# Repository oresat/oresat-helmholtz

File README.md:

# OreSat Helmholtz Cage

This repo contains design and operating instructions of a Helmholtz Cage, which uses the [Biot Savart Law](https://en.wikipedia.org/wiki/Biot%E2%80%93Savart_law) to get a desired magnetic field inside of an enclosed space using three pairs of perpendicular coils, one pair for each axis. Our fundamental purpose in doing this is to test cubesats' pointing and detumbling capabilities in LEO.

v2.0 is now underway, utilizing less hardware than v1.0. This is excellent news for everyone involved, as less parts means less things that can and will break. We are using a Raspberry Pi Pico to run it, with each set of coils getting their own motor driver, to drive the current, and a INA226 to monitor the current. A full schematic can be found [here](./controller-v2/helmholtz-controller-v2.kicad_sch). A PCB layout is in the works.

# Design Notes

**Status, design, and testing information can be found in the [OreSat Helmholtz Cage Design Notes](https://docs.google.com/document/d/1s9UlxD-V_3-_QfmXqKaY5oYsfC2GDHxeAkWD0VgjS5g/edit?tab=t.0).**

A seperate doc on the structure and design of the cage itself can be found [here](./docs/Open%20Source%20Document.docx). This doc is a bit out of date in some aspects, mainly the technical hardware, but serves as a good resource for cage construction and theory.

## Pictures
MCECS BETA Project 2018:

Current Build:

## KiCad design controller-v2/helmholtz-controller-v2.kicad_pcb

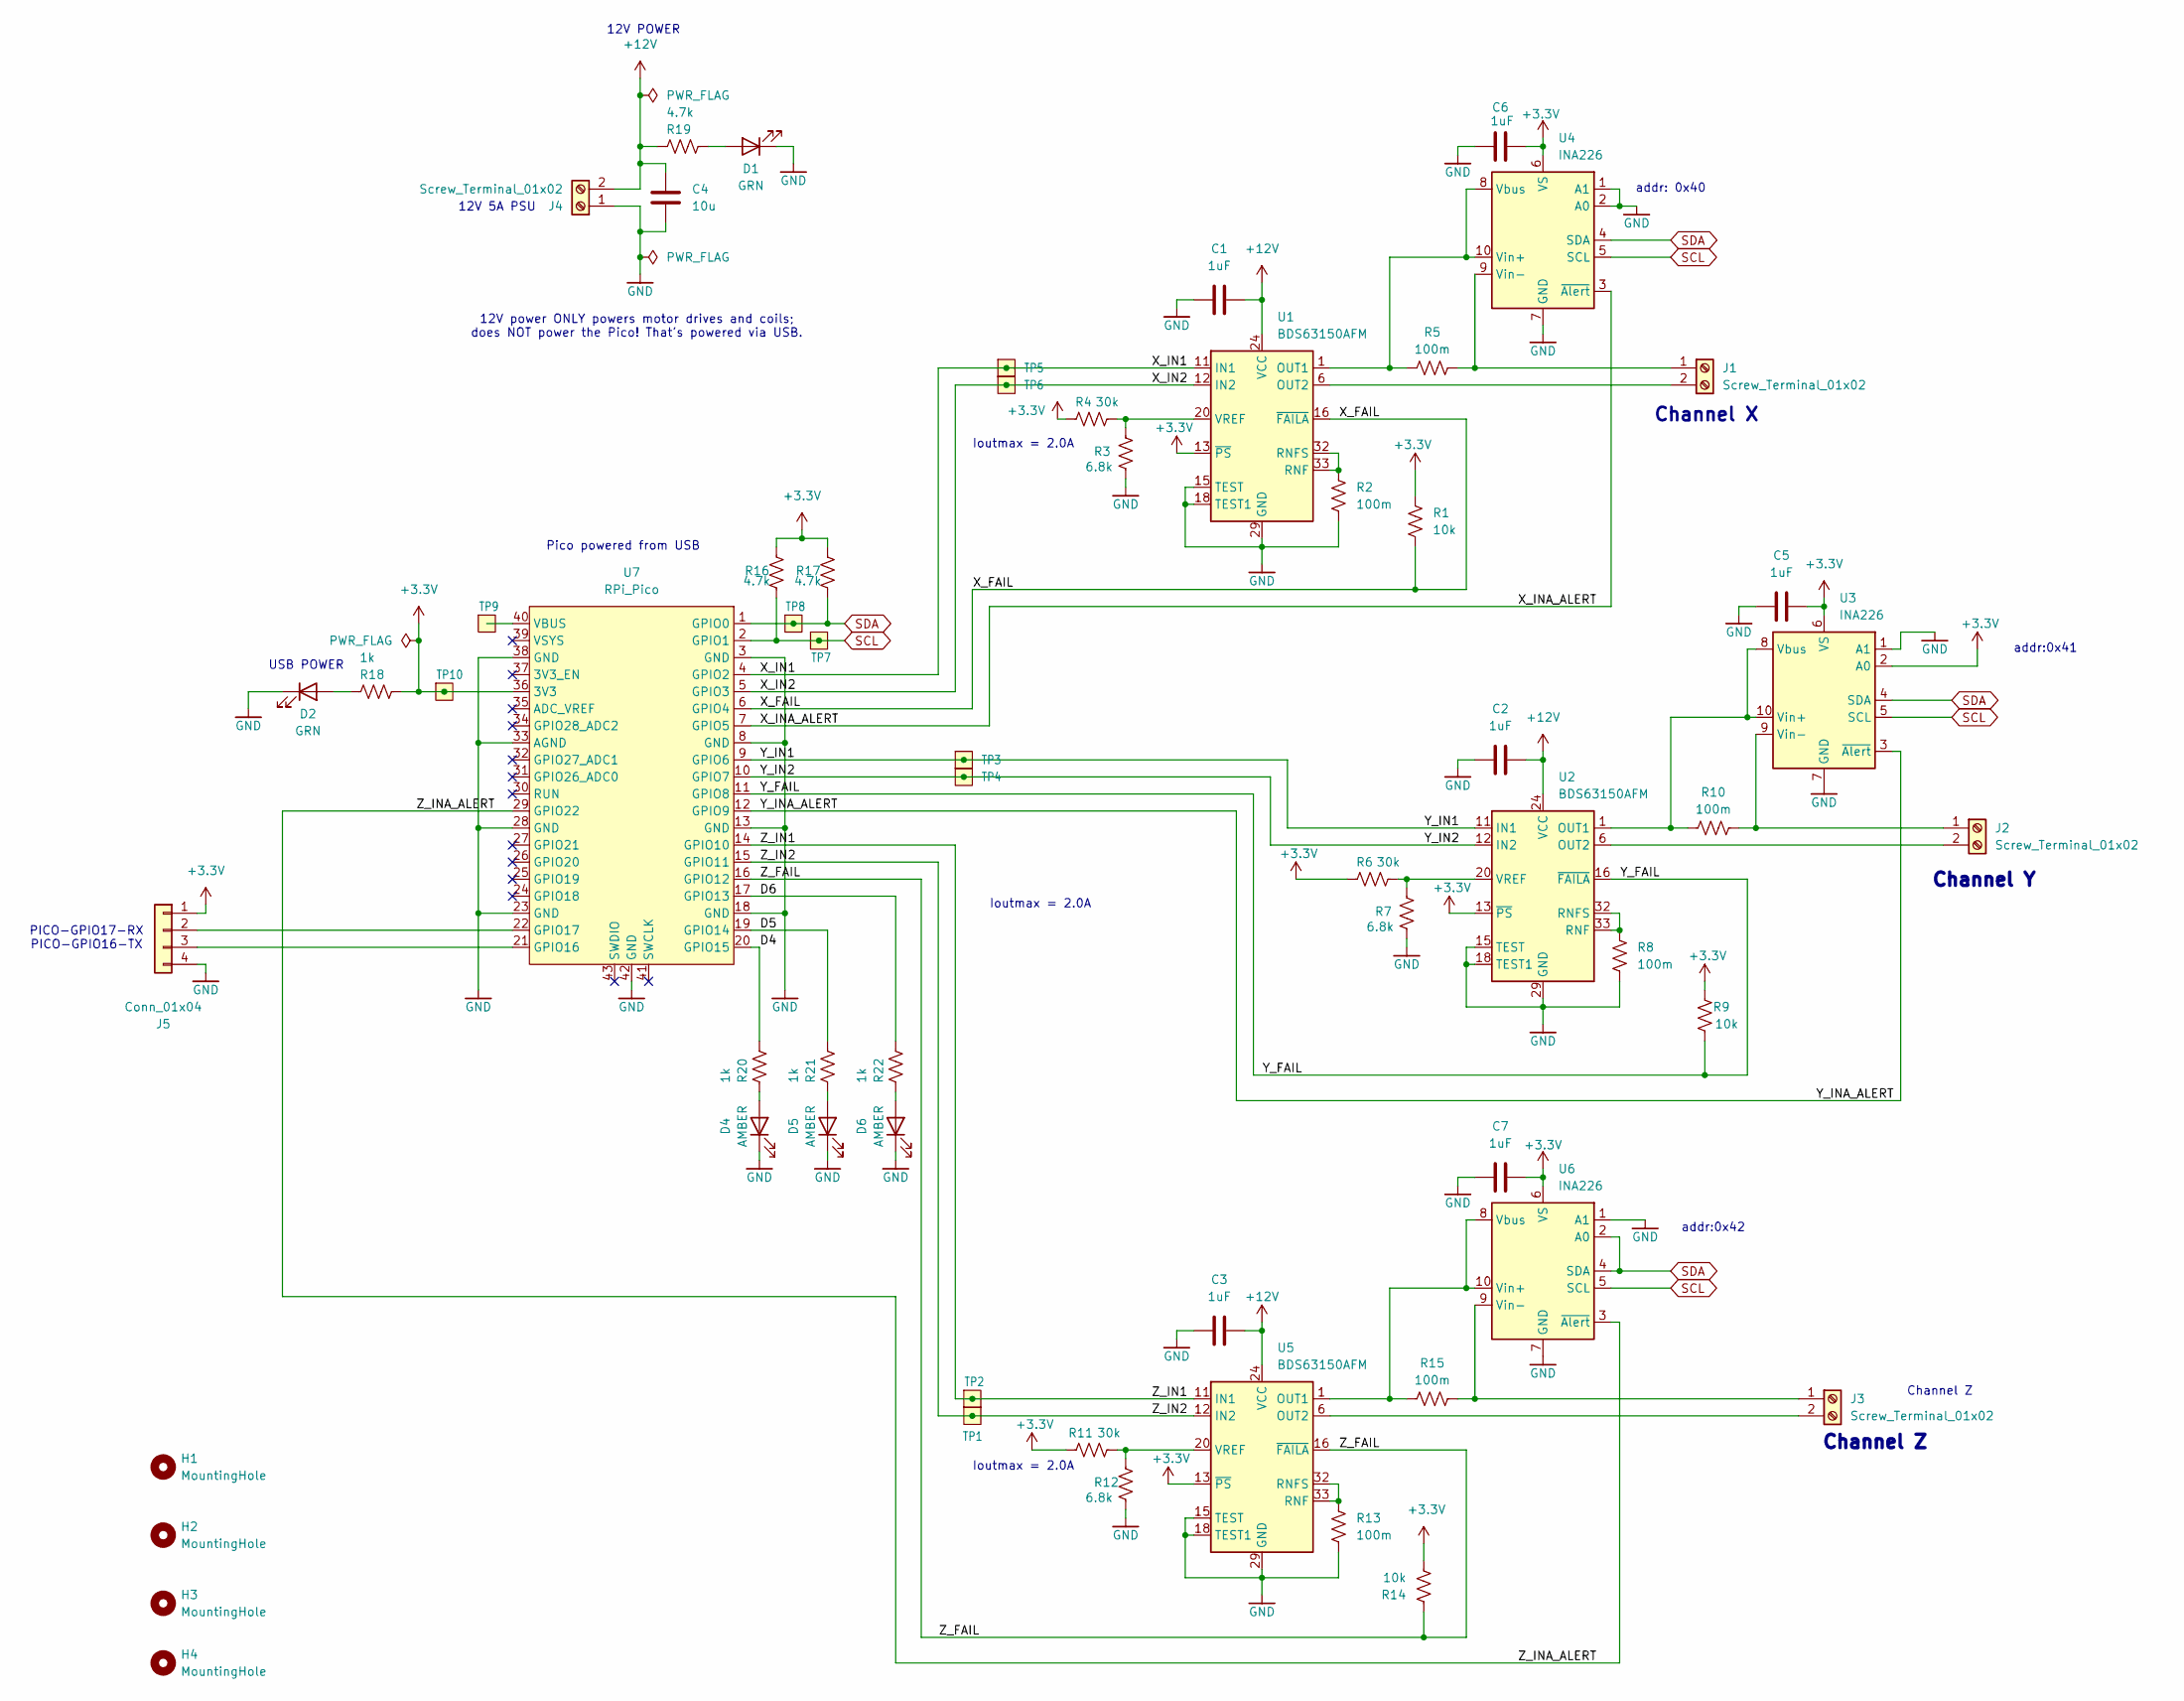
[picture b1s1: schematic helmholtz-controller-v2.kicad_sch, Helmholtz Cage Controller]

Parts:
C1, C2, C3, C5, C6, C7: 1uF; C_0805_2012Metric; MPN CL21B105KAFNNNE
C4: 10u; C_0805_2012Metric; MPN CL21A106KAYNNNE
D1, D2: GRN; LED_0603_1608Metric; MPN IN-S63AT5G
D4, D5, D6: AMBER; LED_0603_1608Metric; MPN IN-S63AT5A
H1, H2, H3, H4: MountingHole; MountingHole_3.2mm_M3
J1, J2, J3, J4: Screw_Terminal_01x02; TerminalBlock_Phoenix_PT-1,5-2-3.5-H_1x02_P3.50mm_Horizontal; MPN 1751248
J5: Conn_01x04; PinHeader_1x04_P2.54mm_Vertical; MPN 0022112042
R1, R9, R14: 10k; R_0603_1608Metric; MPN RMCF0603FT10K0
R2, R5, R8, R10, R13, R15: 100m; R_1206_3216Metric; MPN CSR1206FTR100
R3, R7, R12: 6.8k; R_0603_1608Metric; MPN RC0603JR-076K8L
R4, R6, R11: 30k; R_0603_1608Metric; MPN CRCW060330K0FKEAC
R16, R17, R19: 4.7k; R_0603_1608Metric; MPN RC0603FR-074K7L
R18, R20, R21, R22: 1k; R_0603_1608Metric; MPN RMCF0603FT1K00
TP1, TP2, TP3, TP4, TP5, TP6, TP7, TP8, TP9, TP10: Test-Point; TestPoint-0.75mm-th
U1, U2, U5: BDS63150AFM; U-BD63150AFM; MPN BD63150AFM-E2
U3, U4, U6: INA226; VSSOP-10_3x3mm_P0.5mm; MPN INA226AIDGST
U7: RPi_Pico; RPi_Pico_Castellated; MPN SC0915

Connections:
+3.3V: C5.2, C6.2, C7.2, J5.1, R1.1, R4.1, R6.1, R9.2, R11.1, R14.2, R16.2, R17.2, R18.2, TP10.1, U1.13 (~PS), U2.13 (~PS), U3.2 (A0), U3.6 (VS), U4.6 (VS), U5.13 (~PS), U6.6 (VS), U7.36 (3V3)
+12V: C1.2, C2.2, C3.2, C4.2, J4.2, R19.1, U1.24 (VCC), U1.25 (VCC), U1.26 (VCC), U2.24 (VCC), U2.25 (VCC), U2.26 (VCC), U5.24 (VCC), U5.25 (VCC), U5.26 (VCC)
/D4: R20.2, U7.20 (GPIO15)
/D5: R21.2, U7.19 (GPIO14)
/D6: R22.2, U7.17 (GPIO13)
/X_FAIL: R1.2, U1.16 (~FAILA), U7.6 (GPIO4)
/X_IN1: TP5.1, U1.11 (IN1), U7.4 (GPIO2)
/X_IN2: TP6.1, U1.12 (IN2), U7.5 (GPIO3)
/X_INA_ALERT: U4.3 (~Alert), U7.7 (GPIO5)
/Y_FAIL: R9.1, U2.16 (~FAILA), U7.11 (GPIO8)
/Y_IN1: TP3.1, U2.11 (IN1), U7.9 (GPIO6)
/Y_IN2: TP4.1, U2.12 (IN2), U7.10 (GPIO7)
/Y_INA_ALERT: U3.3 (~Alert), U7.12 (GPIO9)
/Z_FAIL: R14.1, U5.16 (~FAILA), U7.16 (GPIO12)
/Z_IN1: TP2.1, U5.11 (IN1), U7.14 (GPIO10)
/Z_IN2: TP1.1, U5.12 (IN2), U7.15 (GPIO11)
/Z_INA_ALERT: U6.3 (~Alert), U7.29 (GPIO22)
GND: C1.1, C2.1, C3.1, C4.1, C5.1, C6.1, C7.1, D1.1 (K), D2.1 (K), D4.1 (K), D5.1 (K), D6.1 (K), J4.1, J5.4, R2.2, R3.1, R7.1, R8.2, R12.1, R13.2, U1.15 (TEST), U1.18 (TEST1), U1.22 (GND), U1.29 (GND), U1.37 (GND), U1.38 (GND), U2.15 (TEST), U2.18 (TEST1), U2.22 (GND), U2.29 (GND), U2.37 (GND), U2.38 (GND), U3.1 (A1), U3.7 (GND), U4.1 (A1), U4.2 (A0), U4.7 (GND), U5.15 (TEST), U5.18 (TEST1), U5.22 (GND), U5.29 (GND), U5.37 (GND), U5.38 (GND), U6.1 (A1), U6.7 (GND), U7.3 (GND), U7.8 (GND), U7.13 (GND), U7.18 (GND), U7.23 (GND), U7.28 (GND), U7.33 (AGND), U7.38 (GND), U7.42 (GND)
unnamed: D1.2 (A), R19.2
unnamed: D2.2 (A), R18.1
unnamed: D4.2 (A), R20.1
unnamed: D5.2 (A), R21.1
unnamed: D6.2 (A), R22.1
unnamed: J1.1, R5.2, U4.9 (Vin-)
unnamed: J1.2, U1.6 (OUT2), U1.7 (OUT2), U1.8 (OUT2)
unnamed: J2.1, R10.2, U3.9 (Vin-)
unnamed: J2.2, U2.6 (OUT2), U2.7 (OUT2), U2.8 (OUT2)
unnamed: J3.1, R15.2, U6.9 (Vin-)
unnamed: J3.2, U5.6 (OUT2), U5.7 (OUT2), U5.8 (OUT2)
unnamed: J5.2, U7.22 (GPIO17)
unnamed: J5.3, U7.21 (GPIO16)
unnamed: R2.1, U1.32 (RNFS), U1.33 (RNF), U1.34 (RNF), U1.35 (RNF)
unnamed: R3.2, R4.2, U1.20 (VREF)
unnamed: R8.1, U2.32 (RNFS), U2.33 (RNF), U2.34 (RNF), U2.35 (RNF)
unnamed: R6.2, R7.2, U2.20 (VREF)
unnamed: R10.1, U2.1 (OUT1), U2.2 (OUT1), U2.3 (OUT1), U3.8 (Vbus), U3.10 (Vin+)
unnamed: R5.1, U1.1 (OUT1), U1.2 (OUT1), U1.3 (OUT1), U4.8 (Vbus), U4.10 (Vin+)
unnamed: R13.1, U5.32 (RNFS), U5.33 (RNF), U5.34 (RNF), U5.35 (RNF)
unnamed: R11.2, R12.2, U5.20 (VREF)
unnamed: R15.1, U5.1 (OUT1), U5.2 (OUT1), U5.3 (OUT1), U6.8 (Vbus), U6.10 (Vin+)
unnamed: TP9.1, U7.40 (VBUS)
SCL: R16.1, TP7.1, U3.5 (SCL), U4.5 (SCL), U6.5 (SCL), U7.2 (GPIO1)
SDA: R17.1, TP8.1, U3.4 (SDA), U4.4 (SDA), U6.2 (A0), U6.4 (SDA), U7.1 (GPIO0)

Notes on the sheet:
Ioutmax = 2.0A
Channel Z
12V POWER
PICO-GPIO17-RX PICO-GPIO16-TX
Channel X
addr:0x42
addr: 0x40
12V power ONLY powers motor drives and coils; does NOT power the Pico! That's powered via USB.
USB POWER
12V 5A PSU
Channel Y
addr:0x41
Pico powered from USB

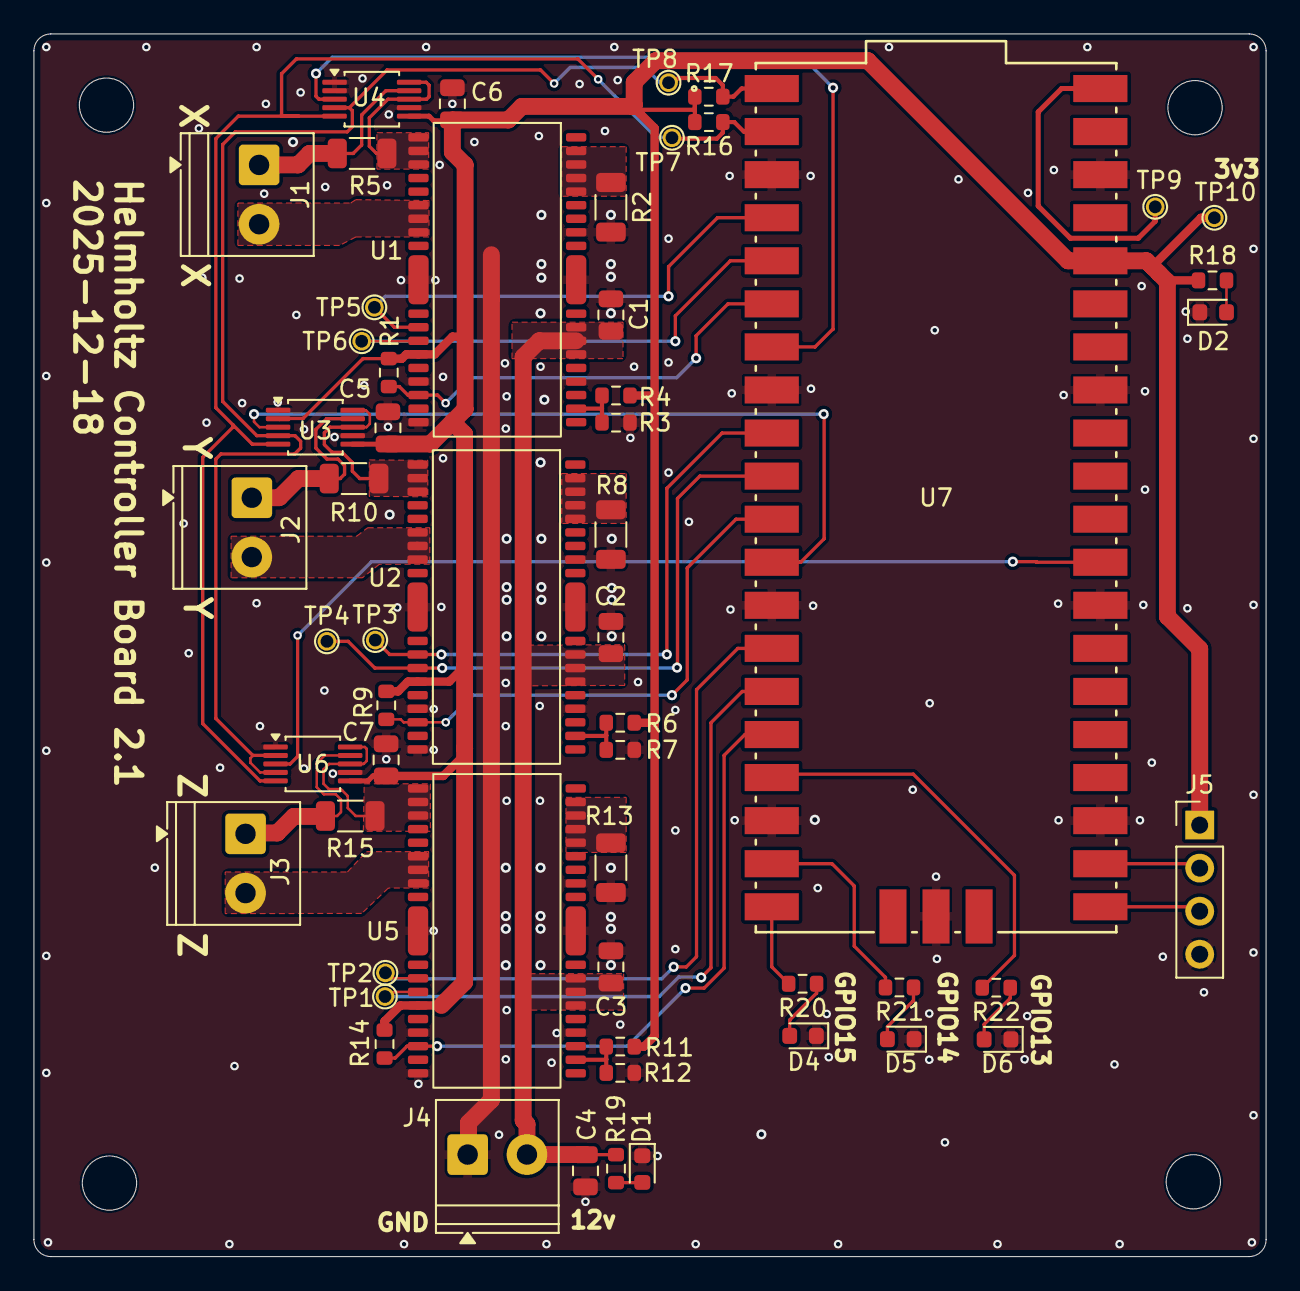
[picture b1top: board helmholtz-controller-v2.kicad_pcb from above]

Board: 2 copper layers, 72.7 x 72.1 mm, 60 parts (0 on the bottom side), 43 nets.

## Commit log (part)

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2019-05-02 fixed psu indexing issue
2019-05-02 anonymous update
2019-09-11 testing new functionality for motor drivers and automatic current setting
2019-09-12 bug fixin
2019-09-13 added sensor reset for magnetometer
2019-10-30 Added Cesar's first version of the distributution board.
2020-01-26 Added mounting holes to VNH boards, put mounting holes on board, and changed font to vector.
2023-01-13 Updated
    Updated with previous edits to remove unnecessary branches.
2023-01-28 Add git hooks
2023-01-28 Add Github Workflows
2023-02-13 Update license to the correct edition: GPLv3
2023-02-19 wrote serial_test.py; should open serial connections to the three PSU's, adjust their voltage and limits and close the connections
2023-02-19 adjusted settings import
2023-02-19 rewrote so that program is killable and reads voltages to screen
2023-05-15 ZXY6005s powersupply library prototype
2023-06-21 Arduino driver WIP
2023-06-23 Arduino Driver WIP v2.3
2023-06-29 Updated Arduino Nano code.
2023-08-03 Powersupply driver
2023-08-04 Reorganized Helmholtz source code files
2023-08-11 Updated Arduino driver v2.5
2023-08-14 Updated Arduino object constructor and main constructor.
2023-08-14 Updated main to work with updated Arduino driver. Removed properties and made them functions.
2023-08-14 Updated psu power function in main.
2023-08-16 Fixed an issue with ZXY6005s return voltage function.
2023-08-21 Rewrote commands for ZXY and changed a mode function.
2023-08-21 Fully functional HC shell. Fixed all bugs
2023-09-14 Added Calibration function help message. WIP
2023-09-14 Fixed typo
2023-09-14 Fixed for loop issues
2024-03-07 Test infrastructure working
    Hardcoded paths to the ttys for the psus is currently required in the
    testing infrastructure. We need to add a fixture to find the devices
    instead of hardcoding them.
    oresat_helmholtz/psu.py is the basis of the rework. Other files under
    oresat_helmholtz/ will likely be removed.
2024-03-07 Add contrib guide
    Add stubs for further documentation, including instructions for linting,
    testing, and installing dependencies needed for development.
2024-07-09 Cleaned up and updated to modern Linux
2024-07-15 added port mapping instructions to readme
2024-07-19 Added serial message on boot and started remove stupid decimal number magic numbers.
2024-07-23 Uncommented magnetometer lines to enable reading in field data.
2024-07-23 set default current and voltage
2024-07-25 commenting out magnetometer stuff... again
2024-08-07 Commented line 329.
2024-08-21 Updated the Helmholtz shell to include helper functions for the new Magnetometer library
2024-08-21 Modified main file to include draft 1 of magnetometer
2024-08-21 Adding the meter USB location as a required argument
2024-08-21 Added missing 'Magnetometer' argument on line 17
2024-08-22 Added missing parameter in meter properties function
2024-08-22 Missing parameter added to the parse_meter_response function
2024-08-22 Changed the value of ID_METER_PROP to a int, not a str.
2024-08-22 Third command draft.
2024-08-23 Draft function for streaming data.
2024-08-27 modified 'parse_data_point()' to print data value as a signed float32
2024-08-27 Prototype parsing data points function. Avoids printing bogus readings.
2024-08-27 address garbage vals avter sleep
2024-08-27 break if garbage readings
2024-08-28 New function added to calculate the average readings of all 3 axes.
2024-08-28 Fixed an issue where the chunk array wasn't defined properly.
2024-08-29 Missing variables for axes average values added.
2024-08-29 Pushing to fix bugs.
2024-08-29 Debug v2
2024-08-29 Reverting back to v2.
2024-08-29 Changing conditional parameters
2024-08-29 average data without garbage
2024-08-29 formatting averaging function
2024-08-29 Created new utilities library. Moved the reading average function into new file.
2024-08-29 Same as last revision
2024-08-29 Begin working on function to zero out the mag. field inside the cage.
2024-08-30 Added 'set_field_vector()' to Helmholtz shell
2024-08-30 Debugging 1
2024-08-30 Fixing array dimensions in utils
2024-08-30 Update PSU calls to use floats
2024-08-30 quick fix again
2024-09-03 removing superfluous comments
2024-09-03 add missing arg
2024-09-03 Added Daniel M.'s code for testing.
2024-09-03 Used square brackets instead of parenthesis
2024-09-03 Debugging target output issue in 'set_field_vector()' v1
2024-09-03 Debug
2024-09-05 removed usused variable
2024-09-05 add debug print statement
2024-09-05 Updating calibration function for linear regression
2024-09-17 Changed calibration function to record magnetometer readings
2024-09-17 Okay using enumerate in the for loops is the smarter way to do it.
2024-09-17 Added sign of magnetometer value
2024-09-20 Updated function arguments and their defaults Added constants `MAG_CURRENT_SLOPE` and `WMM_AMBIENT_FIELD` to use as default conversion factors Added constant `MAX_OUT_CURRENT` used to limit the outpu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
2024-09-20 Move new content to img
2024-09-21 Update README.md
    Updated Photo of the Helmholtz Cage
2024-09-21 Update README.md
    One more time!
2024-09-21 Major update to add manpages for software docs Added arduino.md, hshell.md, magmeter.md, powsups.md, utils.md, and manindex.rst to document HC controller Updated index.rst to include new manpages Upd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
2024-09-21 Major update filling out all function documentation Added documentation for each function in arduino.md, hshell.md, magmeter.md, powsups.md, and utils.md Updated manindex.rst
2024-09-22 Fix indentation mistake
2024-09-24 Added a function to test out Lev's basilisk code.
2024-09-25 Added a function to test our Lev's basilisk code. Replicated a commit originally made by @gcotom
2024-09-26 Update buck converter bus locations
2024-09-26 whoopsie I made a typo
2024-09-26 Previously removed current correction, put it back cause we needed it.
2024-09-27 Removed power up section of set_field_vector
2024-09-27 Adding current conversion back again
2024-10-09 Restructured Serial comm functions write, create, read, send command functions are consolidated into one `send_command` function Power supply class now controls a single unit and takes a location as 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
2024-10-13 Testing, debugging, and updating code for virtual serial port.
2024-10-13 Added calibrate_axis(), is WIP but close
2024-10-13 Calibrate_axis debug
2024-10-13 calibrate_axis debug 3
2024-10-13 calibrate_axis debug again
2024-10-15 Magnetomter communication refactored
2024-10-17 Quick fix for indexing issue in data parsing function
2024-10-20 Making stream_data request data on timeout
2024-10-20 Debug 2
2024-10-20 Fixed function call for calibrate_axis
2024-10-20 debug 3
2024-10-20 Testing new error handling for PSUs
2024-10-27 Adding delays for serial streams
2024-10-27 Remove delays, debugging
2024-10-27 Fix get_value function attempt 1
2024-10-27 Remove current correction term, we may not need it
2024-10-28 Fix call to linear_regression function
2025-01-26 added testing documentation and updated image of cage
2025-03-05 Created schematic for new Helmholtz Cage power driver
2025-03-12 New branch for development of Helmholtz controller V2
2025-03-12 Improved schematic, made it more readable
2025-03-12 Remove temporary kicad files
2025-05-11 Remove merge conflict left in commit
2025-08-15 updated schematic
2025-08-19 Updated schematic & board
2025-08-25 Pre-final review
    UART still needs to be connected
2025-08-27 Final Review Ready
2025-09-13 Alert pins connected to pico
2025-09-14 Added mounting holes to schematic & connected alert pins on PCB.
2025-10-19 Rerouted 3.3v & 12v, added zones
2025-10-20 Filled out BOM
2025-12-21 Test Python scripts for v2 controller card
2026-01-07 Formatting
2026-01-07 Fix errors in INA226 driver
    There was a redefinition of a function that looks unfinished, so I
    removed them both. I assume they were supposed to set calibration
    registers with custom values, but at the moment the purpose of the
    functions were unclear because they were unutilized.
2026-01-08 Create flash script
    Without using circuitpython's recommended Mu editor it's kind of a pain
    to flash. Thus I wrote a bash script to ease the process. This will
    probably need to be a little more robust than this to work across
    everyones computers, but this is at least a start for now.
2026-01-12 Add build process to flash script and rename it to pico-flash
    Compiling to .mpy reduces code size and increases exexcution speed.
    Additionally, the script will now create a build dir if it doesnt exist
    already, make sure the required tools are installed before building, and
    make sure the pico is plugged in before flashing, exiting with an error
    if any steps fail.
2026-01-12 Fix bugs, clean syntax
2026-01-12 use adafruit's logging module, and update pyproject.toml
2026-01-12 Remove mypy support
    It's really not happy with any of this code for some reason, even though
    it's flashing. It's saying things don't exist that very well do. I don't
    want to do any labor to get it to work at the moment. Maybe someday.
2026-01-13 Change motor pins from digital to pwm
2026-01-15 Create MR3 communication bridge sub-project
    This will go on the rpi5 and handle streaming/parsing the data from the
    milligauss meter
2026-01-20 rename milligaus_meter to mr3_reader
    semantics
2026-01-20 WIP cont.
2026-01-21 Arduino and serial bridge work in progress
2026-01-22 Complete mr3_reader code initial version
2026-01-30 Delete mr3_reader/mnt
    I don't know how this got checked into git
2026-02-01 WIP: Fix mr3 read errors
2026-02-02 Remove semicolon
2026-02-02 Update pico uart driver
    We can get rid of the buffer now that we are certain about what were
    getting from the rpi5. It will always be 21 bytes, and it comes in very
    consistently now.
2026-02-02 Reset uart input buffer on error
    Allows uart to recover from errors and prevents infinite loops when
    retrying reading the bridge until success
2026-02-03 delete mr3 cobsr file
    We'll just use the same for both the mr3 and the pico
2026-02-06 WIP: p_loop continued
2026-03-13 Update to schematic
2026-03-22 getting closer to perfect
2026-03-22 Minor cleanup on DRC
2026-03-26 Some polish
2026-04-23 Helholtz cage controller v3.0, upgrade to KICad 10, new gitignore file
2026-05-25 Fix INA226 configuration
    the ina226 comes preconfigured to expect a maximum of 3.2A, but we limit
    the motor drivers to 2A, so we can configure it to expect that. Also,
    RSHUNT was at 10m ohms, which is wrong, its 100m Ohms, so we were
    getting garbage readings.
2026-05-29 Use slow decay mode
    Using slow decay mode fixes the issue with current collapsing ~50% duty
    cycle. This is achieved by pwm-ing the input that would normally be zero
    according to the truth table while keeping the input that would normally
    be high according to the truth table high. This also means we have to do
    a little math on args to the methods ie subtract the desired duty cycle
    from 100.
2026-05-29 Add set dc cli command
    This is a useful debugging command to pwm at a a certain duty cycle a
    specific motor drivers inputs and read it's current output in a loop.
2026-06-08 Restructure project, add library
    This commit moves from a flat layout to a src layout. This move should
    keep things more organized as the project grows. It also installs the
    progressbar library from adafruit. I've updated the Makefile to handle
    these changes as well.
2026-06-17 Use Less Dicts
    because dictionaries aren't ordered in this version of python, using
    them is often not very ergonomic. using lists and tuples instead greatly
    simplifies a lot of things.
    Changes:
    motor driver assemblies list,
    slopes_and_intercepts list,
2026-06-17 rename motor -> motor driver
    for clarity, it's not a motor, its just the driver
